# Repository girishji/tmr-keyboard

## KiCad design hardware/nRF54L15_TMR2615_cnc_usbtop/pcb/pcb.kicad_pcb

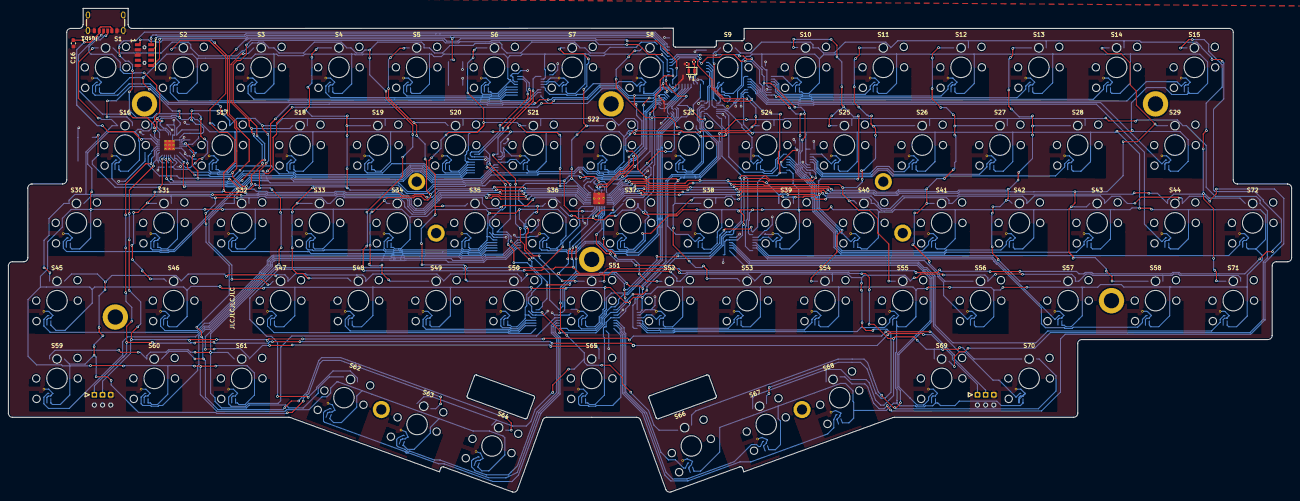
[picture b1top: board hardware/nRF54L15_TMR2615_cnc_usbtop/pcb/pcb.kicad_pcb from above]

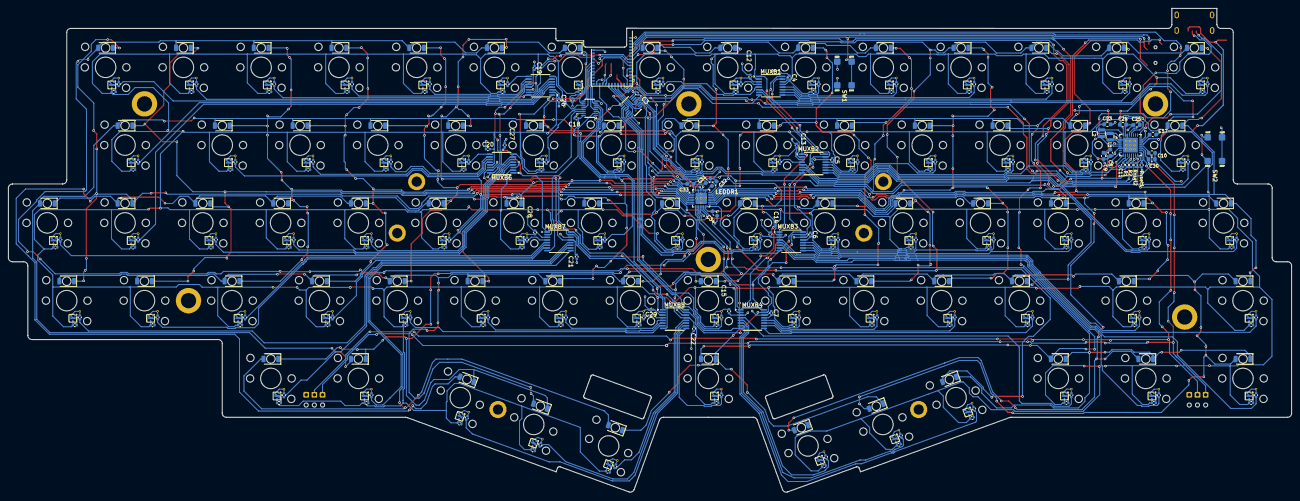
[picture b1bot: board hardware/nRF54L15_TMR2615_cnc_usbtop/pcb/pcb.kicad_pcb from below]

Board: 2 copper layers, 313.5 x 118.2 mm, 435 parts (340 on the bottom side), 142 nets.

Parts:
BAT1, BAT2: PCB_Wire_Solder_3p_Connector
C1, C2: 12pF; C_0402_1005Metric
C3, C4, C5, C6, C7, C12, C13, C14, C15, C18, C19, C20, C21, C22, C26, C27, C28, C29: .1uF; C_0402_1005Metric
C8, C9, C10, C23, C24: 10uF; C_0603_1608Metric
C11: 0.1uF; C_0402_1005Metric
C16, C17, C32, C33, C34: 1uF; C_0603_1608Metric
C25, C30: 2.2uF; C_0603_1608Metric
C31: 1nF; C_0603_1608Metric
Cvcc1, Cvcc2, Cvcc3, Cvcc4, Cvcc5, Cvcc6, Cvcc7, Cvcc8, Cvcc9, Cvcc10, Cvcc11, Cvcc12, Cvcc13, Cvcc14, Cvcc15, Cvcc16, Cvcc17, Cvcc18, Cvcc19, Cvcc20, Cvcc21, Cvcc22, Cvcc23, Cvcc24, Cvcc25, Cvcc26, Cvcc27, Cvcc28, Cvcc29, Cvcc30, Cvcc31, Cvcc32, Cvcc33, Cvcc34, Cvcc35, Cvcc36, Cvcc37, Cvcc38, Cvcc39, Cvcc40, Cvcc41, Cvcc42, Cvcc43, Cvcc44, Cvcc45, Cvcc46, Cvcc47, Cvcc48, Cvcc49, Cvcc50, Cvcc51, Cvcc52, Cvcc53, Cvcc54, Cvcc55, Cvcc56, Cvcc57, Cvcc58, Cvcc59, Cvcc60, Cvcc61, Cvcc62, Cvcc63, Cvcc64, Cvcc65, Cvcc66, Cvcc67, Cvcc68, Cvcc69, Cvcc70, Cvcc71, Cvcc72: 0.1uF; C_0402_1005Metric_Cvcc
Cvout1, Cvout2, Cvout3, Cvout4, Cvout5, Cvout6, Cvout7, Cvout8, Cvout9, Cvout10, Cvout11, Cvout12, Cvout13, Cvout14, Cvout15, Cvout16, Cvout17, Cvout18, Cvout19, Cvout20, Cvout21, Cvout22, Cvout23, Cvout24, Cvout25, Cvout26, Cvout27, Cvout28, Cvout29, Cvout30, Cvout31, Cvout32, Cvout33, Cvout34, Cvout35, Cvout36, Cvout37, Cvout38, Cvout39, Cvout40, Cvout41, Cvout42, Cvout43, Cvout44, Cvout45, Cvout46, Cvout47, Cvout48, Cvout49, Cvout50, Cvout51, Cvout52, Cvout53, Cvout54, Cvout55, Cvout56, Cvout57, Cvout58, Cvout59, Cvout60, Cvout61, Cvout62, Cvout63, Cvout64, Cvout65, Cvout66, Cvout67, Cvout68, Cvout69, Cvout70, Cvout71, Cvout72: 0.1nF; C_0402_1005Metric_Cvout
D1, D2, D3, D4, D5, D6, D7, D8, D9, D10, D11, D12, D13, D14, D15, D16, D17, D18, D19, D20, D21, D22, D23, D24, D25, D26, D27, D28, D29, D30, D31, D32, D33, D34, D35, D36, D37, D38, D39, D40, D41, D42, D43, D44, D45, D46, D47, D48, D49, D50, D51, D52, D53, D54, D55, D56, D57, D58, D59, D60, D61, D62, D63, D64, D65, D66, D67, D68, D69, D70, D71, D72: Green LED; LED_1206_3216Metric_ReverseMount_Hole2.1mm
Hm1, Hm2: M1.4_smtso; SMTSO_M1.4_M1.6
Hs1, Hs2, Hs3, Hs4, Hs5, Hs10: M2_Pad; SMTSO_M2
Hs6, Hs7, Hs8, Hs9: M2_Pad; SMTSO_M1.4_M1.6
JLC1: JLC_Order_Num
JTAG1: Conn_ARM_JTAG_SWD_10; SAMTEC-CLP-105-02-X-D-A
Jusb1: USB_C_Receptacle_PowerOnly_6P; USB_C_Receptacle_GCT_USB4125-xx-x_6P_TopMnt_Horizontal
L1, L2: 2.2uH; L_Samsung_CIGT201610EH2R2MNE
LEDDR1: LP5864; LP5864-VQFN-32-1EP_4x4mm_P0.4mm_EP2.8x2.8mm_ThermalVias
M1: Ezurio BL54L15 (nrf54L15) module; Ezurio_BL54L15_Module
MUXA1, MUXA2: TMUX1574DYY; Texas_DYY0016A_TSOT-23-16_2x4.2mm_P0.5mm
MUXB1, MUXB2, MUXB3, MUXB4, MUXB5, MUXB6, MUXB7, MUXB8: TMUX1108PW; TSSOP-16_4.4x5mm_P0.65mm
PMIC1: nPM1300-QEXX; QFN-32-1EP_5x5mm_P0.5mm_EP3.6x3.6mm_ThermalVias
R1, R2: 10k; R_0402_1005Metric
Rvset1: 47k; R_0402_1005Metric
Rvset2: 4.7k; R_0402_1005Metric
S1, S2, S3, S4, S5, S6, S7, S8, S9, S10, S11, S12, S13, S14, S15, S16, S17, S18, S19, S20, S21, S22, S23, S24, S25, S26, S27, S28, S29, S30, S31, S32, S33, S34, S35, S36, S37, S38, S39, S40, S41, S42, S43, S44, S45, S46, S47, S48, S49, S50, S51, S52, S53, S54, S55, S56, S57, S58, S59, S60, S61, S62, S63, S64, S65, S66, S67, S68, S69, S70, S71, S72: Switch; Kailh_gateron_sw_lowpro
SW1, SW2: SW_DIP_x01; Aliexpress_SW_TACT_4x4x1.5mm
Stb1, Stb2: TMR_switch_stab_2.0u; Stabilizer_Lowpro_2U
TMR1, TMR2, TMR3, TMR4, TMR5, TMR6, TMR7, TMR8, TMR9, TMR10, TMR11, TMR12, TMR13, TMR14, TMR15, TMR16, TMR17, TMR18, TMR19, TMR20, TMR21, TMR22, TMR23, TMR24, TMR25, TMR26, TMR27, TMR28, TMR29, TMR30, TMR31, TMR32, TMR33, TMR34, TMR35, TMR36, TMR37, TMR38, TMR39, TMR40, TMR41, TMR42, TMR43, TMR44, TMR45, TMR46, TMR47, TMR48, TMR49, TMR50, TMR51, TMR52, TMR53, TMR54, TMR55, TMR56, TMR57, TMR58, TMR59, TMR60, TMR61, TMR62, TMR63, TMR64, TMR65, TMR66, TMR67, TMR68, TMR69, TMR70, TMR71, TMR72: TMR2615; TMR2615-DFN-3L-1.6x1.6
Y1: 32.768 kHz; Crystal_SMD_2012-2Pin_2.0x1.2mm

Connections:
/AIN0: M1.23 (P1.04/AIN0/CLK), MUXA1.4 (D1)
/AIN1: M1.22 (P1.05/AIN1), MUXA1.7 (D2)
/AIN2: M1.21 (P1.06/AIN2), MUXA1.9 (D3)
/AIN3: M1.20 (P1.07/AIN3), MUXA1.12 (D4)
/AIN4: M1.35 (P1.11/AIN4/CLK), MUXA2.9 (D3)
/AIN5: M1.34 (P1.12/AIN5/CLK), MUXA2.12 (D4)
/AIN6: M1.33 (P1.13/AIN6), MUXA2.4 (D1)
/AIN7: M1.32 (P1.14/AIN7), MUXA2.7 (D2)
/ANA_01: Cvout1.1, MUXB1.7 (S4), TMR1.1 (V_{OUT})
/ANA_02: Cvout2.1, MUXB1.6 (S3), TMR2.1 (V_{OUT})
/ANA_03: Cvout3.1, MUXB1.9 (S8), TMR3.1 (V_{OUT})
/ANA_04: Cvout4.1, MUXB1.10 (S7), TMR4.1 (V_{OUT})
/ANA_05: Cvout5.1, MUXB1.11 (S6), TMR5.1 (V_{OUT})
/ANA_06: Cvout6.1, MUXB1.12 (S5), TMR6.1 (V_{OUT})
/ANA_07: Cvout7.1, MUXB1.4 (S1), TMR7.1 (V_{OUT})
/ANA_08: Cvout8.1, MUXB1.5 (S2), TMR8.1 (V_{OUT})
/ANA_09: Cvout9.1, MUXA2.10 (S3B), TMR9.1 (V_{OUT})
/ANA_10: Cvout10.1, MUXB5.9 (S8), TMR10.1 (V_{OUT})
/ANA_11: Cvout11.1, MUXB5.10 (S7), TMR11.1 (V_{OUT})
/ANA_12: Cvout12.1, MUXB5.11 (S6), TMR12.1 (V_{OUT})
/ANA_13: Cvout13.1, MUXB5.12 (S5), TMR13.1 (V_{OUT})
/ANA_14: Cvout14.1, MUXB5.7 (S4), TMR14.1 (V_{OUT})
/ANA_15: Cvout15.1, MUXB5.6 (S3), TMR15.1 (V_{OUT})
/ANA_16: Cvout16.1, MUXB2.5 (S2), TMR16.1 (V_{OUT})
/ANA_17: Cvout17.1, MUXB2.9 (S8), TMR17.1 (V_{OUT})
/ANA_18: Cvout18.1, MUXB2.10 (S7), TMR18.1 (V_{OUT})
/ANA_19: Cvout19.1, MUXB2.11 (S6), TMR19.1 (V_{OUT})
/ANA_20: Cvout20.1, MUXB2.12 (S5), TMR20.1 (V_{OUT})
/ANA_21: Cvout21.1, MUXB2.4 (S1), TMR21.1 (V_{OUT})
/ANA_22: Cvout22.1, MUXA1.13 (S4B), TMR22.1 (V_{OUT})
/ANA_23: Cvout23.1, MUXA2.6 (S2B), TMR23.1 (V_{OUT})
/ANA_24: Cvout24.1, MUXA2.13 (S4B), TMR24.1 (V_{OUT})
/ANA_25: Cvout25.1, MUXB6.9 (S8), TMR25.1 (V_{OUT})
/ANA_26: Cvout26.1, MUXB6.10 (S7), TMR26.1 (V_{OUT})
/ANA_27: Cvout27.1, MUXB6.11 (S6), TMR27.1 (V_{OUT})
/ANA_28: Cvout28.1, MUXB6.12 (S5), TMR28.1 (V_{OUT})
/ANA_29: Cvout29.1, MUXB5.5 (S2), TMR29.1 (V_{OUT})
/ANA_30: Cvout30.1, MUXB2.7 (S4), TMR30.1 (V_{OUT})
/ANA_31: Cvout31.1, MUXB2.6 (S3), TMR31.1 (V_{OUT})
/ANA_32: Cvout32.1, MUXB3.9 (S8), TMR32.1 (V_{OUT})
/ANA_33: Cvout33.1, MUXB3.10 (S7), TMR33.1 (V_{OUT})
/ANA_34: Cvout34.1, MUXB3.11 (S6), TMR34.1 (V_{OUT})
/ANA_35: Cvout35.1, MUXB3.12 (S5), TMR35.1 (V_{OUT})
/ANA_36: Cvout36.1, MUXA1.6 (S2B), TMR36.1 (V_{OUT})
/ANA_37: Cvout37.1, MUXA1.10 (S3B), TMR37.1 (V_{OUT})
/ANA_38: Cvout38.1, MUXA2.3 (S1B), TMR38.1 (V_{OUT})
/ANA_39: Cvout39.1, MUXB7.4 (S1), TMR39.1 (V_{OUT})
/ANA_40: Cvout40.1, MUXB6.7 (S4), TMR40.1 (V_{OUT})
/ANA_41: Cvout41.1, MUXB6.6 (S3), TMR41.1 (V_{OUT})
/ANA_42: Cvout42.1, MUXB6.5 (S2), TMR42.1 (V_{OUT})
/ANA_43: Cvout43.1, MUXB6.4 (S1), TMR43.1 (V_{OUT})
/ANA_44: Cvout44.1, MUXB5.4 (S1), TMR44.1 (V_{OUT})
/ANA_45: Cvout45.1, MUXB3.5 (S2), TMR45.1 (V_{OUT})
/ANA_46: Cvout46.1, MUXB3.4 (S1), TMR46.1 (V_{OUT})
/ANA_47: Cvout47.1, MUXB4.9 (S8), TMR47.1 (V_{OUT})
/ANA_48: Cvout48.1, MUXB4.10 (S7), TMR48.1 (V_{OUT})
/ANA_49: Cvout49.1, MUXB4.11 (S6), TMR49.1 (V_{OUT})
/ANA_50: Cvout50.1, MUXB4.12 (S5), TMR50.1 (V_{OUT})
/ANA_51: Cvout51.1, MUXA1.3 (S1B), TMR51.1 (V_{OUT})
/ANA_52: Cvout52.1, MUXB8.4 (S1), TMR52.1 (V_{OUT})
/ANA_53: Cvout53.1, MUXB8.5 (S2), TMR53.1 (V_{OUT})
/ANA_54: Cvout54.1, MUXB8.6 (S3), TMR54.1 (V_{OUT})
/ANA_55: Cvout55.1, MUXB8.7 (S4), TMR55.1 (V_{OUT})
/ANA_56: Cvout56.1, MUXB7.12 (S5), TMR56.1 (V_{OUT})
/ANA_57: Cvout57.1, MUXB7.6 (S3), TMR57.1 (V_{OUT})
/ANA_58: Cvout58.1, MUXB7.7 (S4), TMR58.1 (V_{OUT})
/ANA_59: Cvout59.1, MUXB3.6 (S3), TMR59.1 (V_{OUT})
/ANA_60: Cvout60.1, MUXB3.7 (S4), TMR60.1 (V_{OUT})
/ANA_61: Cvout61.1, MUXB4.4 (S1), TMR61.1 (V_{OUT})
/ANA_62: Cvout62.1, MUXB4.7 (S4), TMR62.1 (V_{OUT})
/ANA_63: Cvout63.1, MUXB4.6 (S3), TMR63.1 (V_{OUT})
/ANA_64: Cvout64.1, MUXB4.5 (S2), TMR64.1 (V_{OUT})
/ANA_65: Cvout65.1, MUXB8.9 (S8), TMR65.1 (V_{OUT})
/ANA_66: Cvout66.1, MUXB8.12 (S5), TMR66.1 (V_{OUT})
/ANA_67: Cvout67.1, MUXB8.11 (S6), TMR67.1 (V_{OUT})
/ANA_68: Cvout68.1, MUXB8.10 (S7), TMR68.1 (V_{OUT})
/ANA_69: Cvout69.1, MUXB7.9 (S8), TMR69.1 (V_{OUT})
/ANA_70: Cvout70.1, MUXB7.10 (S7), TMR70.1 (V_{OUT})
/ANA_71: Cvout71.1, MUXB7.11 (S6), TMR71.1 (V_{OUT})
/ANA_72: Cvout72.1, MUXB7.5 (S2), TMR72.1 (V_{OUT})
/CS0: D9.1 (K), D24.1 (K), D38.1 (K), D53.1 (K), LEDDR1.2 (CS0)
/CS1: D10.1 (K), D25.1 (K), D39.1 (K), D54.1 (K), LEDDR1.3 (CS1)
/CS2: D11.1 (K), D26.1 (K), D40.1 (K), D55.1 (K), LEDDR1.4 (CS2)
/CS3: D12.1 (K), D27.1 (K), D41.1 (K), D56.1 (K), LEDDR1.5 (CS3)
/CS4: D13.1 (K), D28.1 (K), D42.1 (K), D57.1 (K), LEDDR1.6 (CS4)
/CS5: D14.1 (K), D29.1 (K), D43.1 (K), D58.1 (K), LEDDR1.7 (CS5)
/CS6: D15.1 (K), D44.1 (K), D71.1 (K), D72.1 (K), LEDDR1.8 (CS6)
/CS7: D67.1 (K), D68.1 (K), D69.1 (K), D70.1 (K), LEDDR1.9 (CS7)
/CS8: D63.1 (K), D64.1 (K), D65.1 (K), D66.1 (K), LEDDR1.10 (CS8)
/CS9: D59.1 (K), D60.1 (K), D61.1 (K), D62.1 (K), LEDDR1.16 (CS9)
/CS10: D1.1 (K), D16.1 (K), D30.1 (K), D45.1 (K), LEDDR1.17 (CS10)
/CS11: D2.1 (K), D17.1 (K), D31.1 (K), D46.1 (K), LEDDR1.18 (CS11)
/CS12: D3.1 (K), D18.1 (K), D32.1 (K), D47.1 (K), LEDDR1.19 (CS12)
/CS13: D4.1 (K), D19.1 (K), D33.1 (K), D48.1 (K), LEDDR1.20 (CS13)
/CS14: D5.1 (K), D20.1 (K), D34.1 (K), D49.1 (K), LEDDR1.21 (CS14)
/CS15: D6.1 (K), D21.1 (K), D35.1 (K), D50.1 (K), LEDDR1.22 (CS15)
/CS16: D7.1 (K), D22.1 (K), D36.1 (K), D51.1 (K), LEDDR1.23 (CS16)
/CS17: D8.1 (K), D23.1 (K), D37.1 (K), D52.1 (K), LEDDR1.24 (CS17)
/GPIO_X: M1.4 (P2.07), PMIC1.10 (GPIO3)
/INT: M1.17 (P0.00), PMIC1.8 (GPIO1)
/LED_DR_EN: C31.1, LEDDR1.32 (VIO_EN), M1.11 (P2.04)
/LOADSW_CTRL: M1.12 (P2.05), PMIC1.9 (GPIO2)
/MUXA_SEL: M1.13 (P2.03), MUXA1.1 (SEL), MUXA2.1 (SEL)
/MUXB_SEL_0: M1.9 (P2.00), MUXB1.1 (A0), MUXB2.1 (A0), MUXB3.1 (A0), MUXB4.1 (A0), MUXB5.1 (A0), MUXB6.1 (A0), MUXB7.1 (A0), MUXB8.1 (A0)
/MUXB_SEL_1: M1.10 (P2.01/CLK), MUXB1.16 (A1), MUXB2.16 (A1), MUXB3.16 (A1), MUXB4.16 (A1), MUXB5.16 (A1), MUXB6.16 (A1), MUXB7.16 (A1), MUXB8.16 (A1)
/MUXB_SEL_2: M1.8 (P2.02), MUXB1.15 (A2), MUXB2.15 (A2), MUXB3.15 (A2), MUXB4.15 (A2), MUXB5.15 (A2), MUXB6.15 (A2), MUXB7.15 (A2), MUXB8.15 (A2)
/MUX_B_1: MUXA1.14 (S4A), MUXB1.8 (D)
/MUX_B_2: MUXA1.11 (S3A), MUXB2.8 (D)
/MUX_B_3: MUXA1.5 (S2A), MUXB3.8 (D)
/MUX_B_4: MUXA1.2 (S1A), MUXB4.8 (D)
/MUX_B_5: MUXA2.11 (S3A), MUXB5.8 (D)
/MUX_B_6: MUXA2.14 (S4A), MUXB6.8 (D)
/MUX_B_7: MUXA2.2 (S1A), MUXB7.8 (D)
/MUX_B_8: MUXA2.5 (S2A), MUXB8.8 (D)
/NRESET: JTAG1.10 (~RESET), M1.7 (NRESET), SW1.2
/SCL: LEDDR1.28 (SCL_SCLK), M1.18 (P0.01), PMIC1.14 (SCL), R1.2
/SDA: LEDDR1.29 (SDA_MOSI), M1.19 (P0.02), PMIC1.13 (SDA), R2.2
/SW0: D1.2 (A), D2.2 (A), D3.2 (A), D4.2 (A), D5.2 (A), D6.2 (A), D7.2 (A), D8.2 (A), D9.2 (A), D10.2 (A), D11.2 (A), D12.2 (A), D13.2 (A), D14.2 (A), D15.2 (A), D62.2 (A), D66.2 (A), D70.2 (A), LEDDR1.11 (SW0)
/SW1: D16.2 (A), D17.2 (A), D18.2 (A), D19.2 (A), D20.2 (A), D21.2 (A), D22.2 (A), D23.2 (A), D24.2 (A), D25.2 (A), D26.2 (A), D27.2 (A), D28.2 (A), D29.2 (A), D61.2 (A), D65.2 (A), D69.2 (A), D72.2 (A), LEDDR1.12 (SW1)
/SW2: D30.2 (A), D31.2 (A), D32.2 (A), D33.2 (A), D34.2 (A), D35.2 (A), D36.2 (A), D37.2 (A), D38.2 (A), D39.2 (A), D40.2 (A), D41.2 (A), D42.2 (A), D43.2 (A), D44.2 (A), D60.2 (A), D64.2 (A), D68.2 (A), LEDDR1.13 (SW2)
/SW3: D45.2 (A), D46.2 (A), D47.2 (A), D48.2 (A), D49.2 (A), D50.2 (A), D51.2 (A), D52.2 (A), D53.2 (A), D54.2 (A), D55.2 (A), D56.2 (A), D57.2 (A), D58.2 (A), D59.2 (A), D63.2 (A), D67.2 (A), D71.2 (A), LEDDR1.14 (SW3)
/SWDCLK: JTAG1.4 (SWCLK/TCK), M1.6 (SWDCLK)
/SWDIO: JTAG1.2 (SWDIO/TMS), M1.5 (SWDIO)
/VBAT: BAT1.1 (VBAT), BAT2.1 (VBAT), C30.1, PMIC1.19 (VBAT)
/VBUSOUT: C17.1, PMIC1.22 (VBUSOUT)
/VDD_nRF: C11.2, C23.1, JTAG1.1 (VTref), L1.1, M1.26 (VDD_nRF), PMIC1.1 (VOUT1), PMIC1.12 (VDDIO), R1.1, R2.1
/VOUT2: C24.1, L2.1, PMIC1.28 (LSIN1/VINLDO1), PMIC1.32 (VOUT2)
/VSYS: C8.1, C9.1, C10.1, C33.1, C34.1, LEDDR1.1 (VCC), LEDDR1.15 (VLED), PMIC1.4 (PVDD), PMIC1.20 (VSYS)
GND: BAT1.3 (GND), BAT2.3 (GND), C1.2, C2.2, C3.1, C4.1, C5.1, C6.1, C7.1, C8.2, C9.2, C10.2, C11.1, C12.1, C12.2, C13.1, C13.2, C14.1, C14.2, C15.1, C15.2, C16.2, C17.2, C18.1, C19.1, C20.1, C21.1, C22.1, C23.2, C24.2, C25.2, C26.1, C26.2, C27.1, C27.2, C28.1, C28.2, C29.1, C29.2, C30.2, C31.2, C32.1, C33.2, C34.2, Cvcc1.2, Cvcc2.2, Cvcc3.2, Cvcc4.2, Cvcc5.2, Cvcc6.2, Cvcc7.2, Cvcc8.2, Cvcc9.2, Cvcc10.2, Cvcc11.2, Cvcc12.2, Cvcc13.2, Cvcc14.2, Cvcc15.2, Cvcc16.2, Cvcc17.2, Cvcc18.2, Cvcc19.2, Cvcc20.2, Cvcc21.2, Cvcc22.2, Cvcc23.2, Cvcc24.2, Cvcc25.2, Cvcc26.2, Cvcc27.2, Cvcc28.2, Cvcc29.2, Cvcc30.2, Cvcc31.2, Cvcc32.2, Cvcc33.2, Cvcc34.2, Cvcc35.2, Cvcc36.2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
unnamed: BAT1.2 (NTC), BAT2.2 (NTC), PMIC1.18 (NTC)
unnamed: Jusb1.A5 (CC1), PMIC1.23 (CC1)
unnamed: Jusb1.B5 (CC2), PMIC1.24 (CC2)
unnamed: C32.2, LEDDR1.25 (VCAP)
unnamed: C1.1, M1.25 (P1.00/XL1), Y1.1
unnamed: C2.1, M1.24 (P1.01/XL2), Y1.2
unnamed: PMIC1.15 (SHPHLD), SW2.2
unnamed: L1.2, PMIC1.3 (SW1)
unnamed: L2.2, PMIC1.5 (SW2)
unnamed: C16.1, Jusb1.A9 (VBUS), Jusb1.B9 (VBUS), PMIC1.21 (VBUS)
unnamed: PMIC1.17 (VSET1), Rvset1.2
unnamed: PMIC1.16 (VSET2), Rvset2.2
VCCS: C3.2, C4.2, C5.2, C6.2, C7.2, C18.2, C19.2, C20.2, C21.2, C22.2, C25.1, Cvcc1.1, Cvcc2.1, Cvcc3.1, Cvcc4.1, Cvcc5.1, Cvcc6.1, Cvcc7.1, Cvcc8.1, Cvcc9.1, Cvcc10.1, Cvcc11.1, Cvcc12.1, Cvcc13.1, Cvcc14.1, Cvcc15.1, Cvcc16.1, Cvcc17.1, Cvcc18.1, Cvcc19.1, Cvcc20.1, Cvcc21.1, Cvcc22.1, Cvcc23.1, Cvcc24.1, Cvcc25.1, Cvcc26.1, Cvcc27.1, Cvcc28.1, Cvcc29.1, Cvcc30.1, Cvcc31.1, Cvcc32.1, Cvcc33.1, Cvcc34.1, Cvcc35.1, Cvcc36.1, Cvcc37.1, Cvcc38.1, Cvcc39.1, Cvcc40.1, Cvcc41.1, Cvcc42.1, Cvcc43.1, Cvcc44.1, Cvcc45.1, Cvcc46.1, Cvcc47.1, Cvcc48.1, Cvcc49.1, Cvcc50.1, Cvcc51.1, Cvcc52.1, Cvcc53.1, Cvcc54.1, Cvcc55.1, Cvcc56.1, Cvcc57.1, Cvcc58.1, Cvcc59.1, Cvcc60.1, Cvcc61.1, Cvcc62.1, Cvcc63.1, Cvcc64.1, Cvcc65.1, Cvcc66.1, Cvcc67.1, Cvcc68.1, Cvcc69.1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

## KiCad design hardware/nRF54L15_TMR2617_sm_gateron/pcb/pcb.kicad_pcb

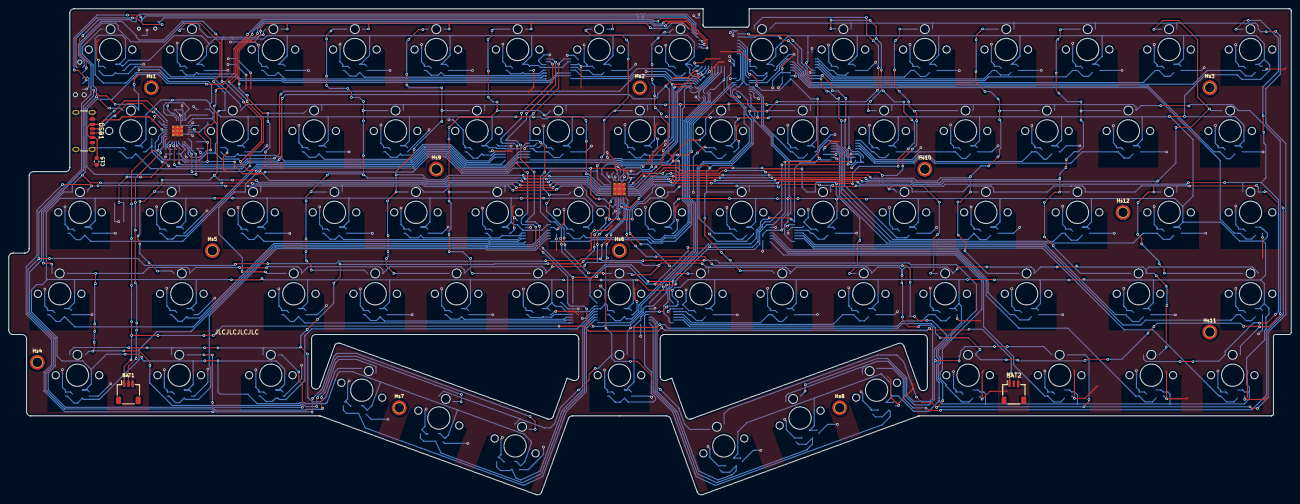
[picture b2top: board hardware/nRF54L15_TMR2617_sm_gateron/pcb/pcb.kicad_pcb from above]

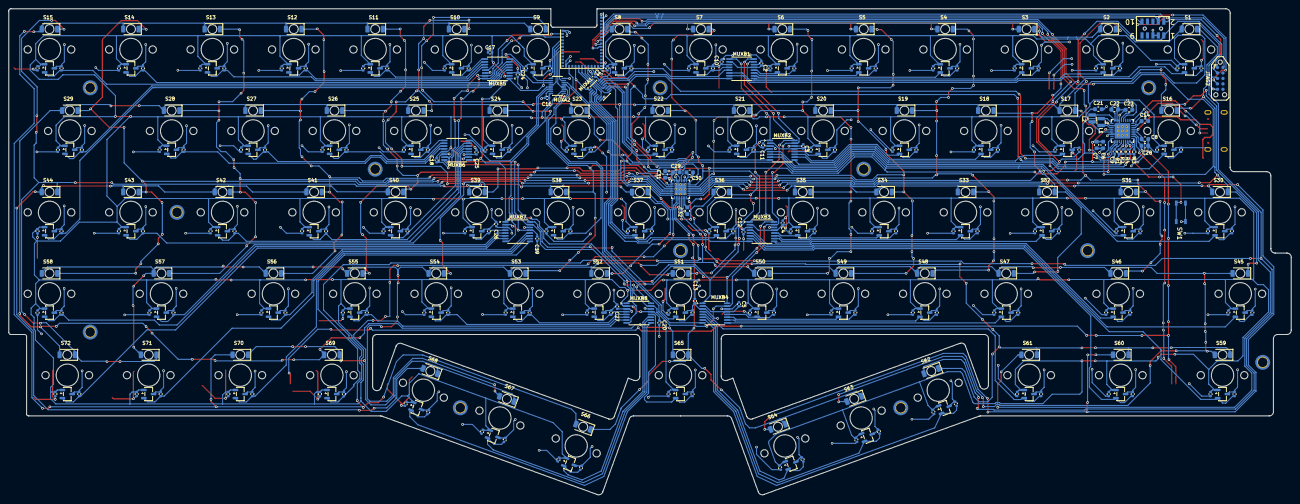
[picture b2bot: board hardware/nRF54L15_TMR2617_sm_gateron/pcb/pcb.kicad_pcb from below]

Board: 2 copper layers, 299.2 x 113.4 mm, 432 parts (341 on the bottom side), 140 nets.

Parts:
BAT1, BAT2: JST_SH_SM03B-SRSS-TB_1x03-1MP_P1.00mm_Horizontal
C1, C2, C3, C4, C5, C10, C11, C12, C13, C16, C17, C18, C19, C20, C24, C25, C26, C27: .1uF; C_0402_1005Metric
C6, C7, C8, C21, C22: 10uF; C_0603_1608Metric
C9: 0.1uF; C_0402_1005Metric
C14, C15, C30, C31, C32: 1uF; C_0603_1608Metric
C23, C28: 2.2uF; C_0603_1608Metric
C29: 1nF; C_0603_1608Metric
Cvcc1, Cvcc2, Cvcc3, Cvcc4, Cvcc5, Cvcc6, Cvcc7, Cvcc8, Cvcc9, Cvcc10, Cvcc11, Cvcc12, Cvcc13, Cvcc14, Cvcc15, Cvcc16, Cvcc17, Cvcc18, Cvcc19, Cvcc20, Cvcc21, Cvcc22, Cvcc23, Cvcc24, Cvcc25, Cvcc26, Cvcc27, Cvcc28, Cvcc29, Cvcc30, Cvcc31, Cvcc32, Cvcc33, Cvcc34, Cvcc35, Cvcc36, Cvcc37, Cvcc38, Cvcc39, Cvcc40, Cvcc41, Cvcc42, Cvcc43, Cvcc44, Cvcc45, Cvcc46, Cvcc47, Cvcc48, Cvcc49, Cvcc50, Cvcc51, Cvcc52, Cvcc53, Cvcc54, Cvcc55, Cvcc56, Cvcc57, Cvcc58, Cvcc59, Cvcc60, Cvcc61, Cvcc62, Cvcc63, Cvcc64, Cvcc65, Cvcc66, Cvcc67, Cvcc68, Cvcc69, Cvcc70, Cvcc71, Cvcc72: 0.1uF; C_0402_1005Metric
Cvout1, Cvout2, Cvout3, Cvout4, Cvout5, Cvout6, Cvout7, Cvout8, Cvout9, Cvout10, Cvout11, Cvout12, Cvout13, Cvout14, Cvout15, Cvout16, Cvout17, Cvout18, Cvout19, Cvout20, Cvout21, Cvout22, Cvout23, Cvout24, Cvout25, Cvout26, Cvout27, Cvout28, Cvout29, Cvout30, Cvout31, Cvout32, Cvout33, Cvout34, Cvout35, Cvout36, Cvout37, Cvout38, Cvout39, Cvout40, Cvout41, Cvout42, Cvout43, Cvout44, Cvout45, Cvout46, Cvout47, Cvout48, Cvout49, Cvout50, Cvout51, Cvout52, Cvout53, Cvout54, Cvout55, Cvout56, Cvout57, Cvout58, Cvout59, Cvout60, Cvout61, Cvout62, Cvout63, Cvout64, Cvout65, Cvout66, Cvout67, Cvout68, Cvout69, Cvout70, Cvout71, Cvout72: 0.1nF; C_0402_1005Metric
D1, D2, D3, D4, D5, D6, D7, D8, D9, D10, D11, D12, D13, D14, D15, D16, D17, D18, D19, D20, D21, D22, D23, D24, D25, D26, D27, D28, D29, D30, D31, D32, D33, D34, D35, D36, D37, D38, D39, D40, D41, D42, D43, D44, D45, D46, D47, D48, D49, D50, D51, D52, D53, D54, D55, D56, D57, D58, D59, D60, D61, D62, D63, D64, D65, D66, D67, D68, D69, D70, D71, D72: Green LED; LED_1206_3216Metric_ReverseMount_Hole2.1mm
Hs1, Hs2, Hs3, Hs4, Hs5, Hs6, Hs7, Hs8, Hs9, Hs10, Hs11, Hs12: M2_Pad; MountingHole_2.2mm_M2_ISO7380_Pad_TopBottom
JLC1: JLC_Order_Num
JTAG1: Conn_02x05_Odd_Even; SAMTEC-CLP-105-02-X-D-A
JTAG2: Conn_02x05_Odd_Even; Tag-Connect_TC2050-IDC-NL_2x05_P1.27mm_Vertical
L1, L2: 2.2uH; L_Samsung_CIGT201610EH2R2MNE
LEDDR1: LP5864; VQFN-32-1EP_4x4mm_P0.4mm_EP2.8x2.8mm_ThermalVias
M1: Ezurio BL54L15 (nrf54L15) module; Ezurio_BL54L15_Module
MUXA1, MUXA2: TMUX1574DYY; Texas_DYY0016A_TSOT-23-16_2x4.2mm_P0.5mm
MUXB1, MUXB2, MUXB3, MUXB4, MUXB5, MUXB6, MUXB7, MUXB8: TMUX1108PW; TSSOP-16_4.4x5mm_P0.65mm
PMIC1: nPM1300-QEXX; QFN-32-1EP_5x5mm_P0.5mm_EP3.6x3.6mm_ThermalVias
R1, R2: 10k; R_0402_1005Metric
R3, R4: 47k; R_0402_1005Metric
S1, S2, S3, S4, S5, S6, S7, S8, S9, S10, S11, S12, S13, S14, S15, S16, S17, S18, S19, S20, S21, S22, S23, S24, S25, S26, S27, S28, S29, S30, S31, S32, S33, S34, S35, S36, S37, S38, S39, S40, S41, S42, S43, S44, S45, S46, S47, S48, S49, S50, S51, S52, S53, S54, S55, S56, S57, S58, S59, S60, S61, S62, S63, S64, S65, S66, S67, S68, S69, S70, S71, S72: Switch; Gateron_Switch_Lowpro
SW1: SW_DIP_x01; Button_Switch_3x4x2.5
Stb1, Stb2: TMR_switch_stab_2.0u; Stabilizer_Lowpro_2U
TMR1, TMR2, TMR3, TMR4, TMR5, TMR6, TMR7, TMR8, TMR9, TMR10, TMR11, TMR12, TMR13, TMR14, TMR15, TMR16, TMR17, TMR18, TMR19, TMR20, TMR21, TMR22, TMR23, TMR24, TMR25, TMR26, TMR27, TMR28, TMR29, TMR30, TMR31, TMR32, TMR33, TMR34, TMR35, TMR36, TMR37, TMR38, TMR39, TMR40, TMR41, TMR42, TMR43, TMR44, TMR45, TMR46, TMR47, TMR48, TMR49, TMR50, TMR51, TMR52, TMR53, TMR54, TMR55, TMR56, TMR57, TMR58, TMR59, TMR60, TMR61, TMR62, TMR63, TMR64, TMR65, TMR66, TMR67, TMR68, TMR69, TMR70, TMR71, TMR72: TMR2617; SOT-23-3
USB1: USB_C_Receptacle_PowerOnly_6P; USB_C_Receptacle_GCT_USB4125-xx-x-0190_6P_TopMnt_Horizontal

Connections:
/AIN0: M1.23 (P1.04/AIN0/CLK), MUXA1.4 (D1)
/AIN1: M1.22 (P1.05/AIN1), MUXA1.7 (D2)
/AIN2: M1.21 (P1.06/AIN2), MUXA1.9 (D3)
/AIN3: M1.20 (P1.07/AIN3), MUXA1.12 (D4)
/AIN4: M1.35 (P1.11/AIN4/CLK), MUXA2.9 (D3)
/AIN5: M1.34 (P1.12/AIN5/CLK), MUXA2.12 (D4)
/AIN6: M1.33 (P1.13/AIN6), MUXA2.4 (D1)
/AIN7: M1.32 (P1.14/AIN7), MUXA2.7 (D2)
/ANA_01: Cvout1.1, MUXB1.7 (S4), TMR1.2 (V_{OUT})
/ANA_02: Cvout2.1, MUXB1.6 (S3), TMR2.2 (V_{OUT})
/ANA_03: Cvout3.1, MUXB1.9 (S8), TMR3.2 (V_{OUT})
/ANA_04: Cvout4.1, MUXB1.10 (S7), TMR4.2 (V_{OUT})
/ANA_05: Cvout5.1, MUXB1.11 (S6), TMR5.2 (V_{OUT})
/ANA_06: Cvout6.1, MUXB1.12 (S5), TMR6.2 (V_{OUT})
/ANA_07: Cvout7.1, MUXB1.4 (S1), TMR7.2 (V_{OUT})
/ANA_08: Cvout8.1, MUXB1.5 (S2), TMR8.2 (V_{OUT})
/ANA_09: Cvout9.1, MUXA2.10 (S3B), TMR9.2 (V_{OUT})
/ANA_10: Cvout10.1, MUXB5.9 (S8), TMR10.2 (V_{OUT})
/ANA_11: Cvout11.1, MUXB5.10 (S7), TMR11.2 (V_{OUT})
/ANA_12: Cvout12.1, MUXB5.11 (S6), TMR12.2 (V_{OUT})
/ANA_13: Cvout13.1, MUXB5.12 (S5), TMR13.2 (V_{OUT})
/ANA_14: Cvout14.1, MUXB5.7 (S4), TMR14.2 (V_{OUT})
/ANA_15: Cvout15.1, MUXB5.6 (S3), TMR15.2 (V_{OUT})
/ANA_16: Cvout16.1, MUXB2.5 (S2), TMR16.2 (V_{OUT})
/ANA_17: Cvout17.1, MUXB2.9 (S8), TMR17.2 (V_{OUT})
/ANA_18: Cvout18.1, MUXB2.10 (S7), TMR18.2 (V_{OUT})
/ANA_19: Cvout19.1, MUXB2.11 (S6), TMR19.2 (V_{OUT})
/ANA_20: Cvout20.1, MUXB2.12 (S5), TMR20.2 (V_{OUT})
/ANA_21: Cvout21.1, MUXB2.4 (S1), TMR21.2 (V_{OUT})
/ANA_22: Cvout22.1, MUXA1.13 (S4B), TMR22.2 (V_{OUT})
/ANA_23: Cvout23.1, MUXA2.6 (S2B), TMR23.2 (V_{OUT})
/ANA_24: Cvout24.1, MUXA2.13 (S4B), TMR24.2 (V_{OUT})
/ANA_25: Cvout25.1, MUXB6.9 (S8), TMR25.2 (V_{OUT})
/ANA_26: Cvout26.1, MUXB6.10 (S7), TMR26.2 (V_{OUT})
/ANA_27: Cvout27.1, MUXB6.11 (S6), TMR27.2 (V_{OUT})
/ANA_28: Cvout28.1, MUXB6.12 (S5), TMR28.2 (V_{OUT})
/ANA_29: Cvout29.1, MUXB5.5 (S2), TMR29.2 (V_{OUT})
/ANA_30: Cvout30.1, MUXB2.7 (S4), TMR30.2 (V_{OUT})
/ANA_31: Cvout31.1, MUXB2.6 (S3), TMR31.2 (V_{OUT})
/ANA_32: Cvout32.1, MUXB3.9 (S8), TMR32.2 (V_{OUT})
/ANA_33: Cvout33.1, MUXB3.10 (S7), TMR33.2 (V_{OUT})
/ANA_34: Cvout34.1, MUXB3.11 (S6), TMR34.2 (V_{OUT})
/ANA_35: Cvout35.1, MUXB3.12 (S5), TMR35.2 (V_{OUT})
/ANA_36: Cvout36.1, MUXA1.6 (S2B), TMR36.2 (V_{OUT})
/ANA_37: Cvout37.1, MUXA1.10 (S3B), TMR37.2 (V_{OUT})
/ANA_38: Cvout38.1, MUXA2.3 (S1B), TMR38.2 (V_{OUT})
/ANA_39: Cvout39.1, MUXB7.4 (S1), TMR39.2 (V_{OUT})
/ANA_40: Cvout40.1, MUXB6.7 (S4), TMR40.2 (V_{OUT})
/ANA_41: Cvout41.1, MUXB6.6 (S3), TMR41.2 (V_{OUT})
/ANA_42: Cvout42.1, MUXB6.5 (S2), TMR42.2 (V_{OUT})
/ANA_43: Cvout43.1, MUXB6.4 (S1), TMR43.2 (V_{OUT})
/ANA_44: Cvout44.1, MUXB5.4 (S1), TMR44.2 (V_{OUT})
/ANA_45: Cvout45.1, MUXB3.5 (S2), TMR45.2 (V_{OUT})
/ANA_46: Cvout46.1, MUXB3.4 (S1), TMR46.2 (V_{OUT})
/ANA_47: Cvout47.1, MUXB4.9 (S8), TMR47.2 (V_{OUT})
/ANA_48: Cvout48.1, MUXB4.10 (S7), TMR48.2 (V_{OUT})
/ANA_49: Cvout49.1, MUXB4.11 (S6), TMR49.2 (V_{OUT})
/ANA_50: Cvout50.1, MUXB4.12 (S5), TMR50.2 (V_{OUT})
/ANA_51: Cvout51.1, MUXA1.3 (S1B), TMR51.2 (V_{OUT})
/ANA_52: Cvout52.1, MUXB8.4 (S1), TMR52.2 (V_{OUT})
/ANA_53: Cvout53.1, MUXB8.5 (S2), TMR53.2 (V_{OUT})
/ANA_54: Cvout54.1, MUXB8.6 (S3), TMR54.2 (V_{OUT})
/ANA_55: Cvout55.1, MUXB8.7 (S4), TMR55.2 (V_{OUT})
/ANA_56: Cvout56.1, MUXB7.12 (S5), TMR56.2 (V_{OUT})
/ANA_57: Cvout57.1, MUXB7.5 (S2), TMR57.2 (V_{OUT})
/ANA_58: Cvout58.1, MUXB7.6 (S3), TMR58.2 (V_{OUT})
/ANA_59: Cvout59.1, MUXB3.6 (S3), TMR59.2 (V_{OUT})
/ANA_60: Cvout60.1, MUXB3.7 (S4), TMR60.2 (V_{OUT})
/ANA_61: Cvout61.1, MUXB4.4 (S1), TMR61.2 (V_{OUT})
/ANA_62: Cvout62.1, MUXB4.7 (S4), TMR62.2 (V_{OUT})
/ANA_63: Cvout63.1, MUXB4.6 (S3), TMR63.2 (V_{OUT})
/ANA_64: Cvout64.1, MUXB4.5 (S2), TMR64.2 (V_{OUT})
/ANA_65: Cvout65.1, MUXB8.12 (S5), TMR65.2 (V_{OUT})
/ANA_66: Cvout66.1, MUXB8.11 (S6), TMR66.2 (V_{OUT})
/ANA_67: Cvout67.1, MUXB8.10 (S7), TMR67.2 (V_{OUT})
/ANA_68: Cvout68.1, MUXB8.9 (S8), TMR68.2 (V_{OUT})
/ANA_69: Cvout69.1, MUXB7.9 (S8), TMR69.2 (V_{OUT})
/ANA_70: Cvout70.1, MUXB7.10 (S7), TMR70.2 (V_{OUT})
/ANA_71: Cvout71.1, MUXB7.11 (S6), TMR71.2 (V_{OUT})
/ANA_72: Cvout72.1, MUXB7.7 (S4), TMR72.2 (V_{OUT})
/CS0: D9.1 (K), D24.1 (K), D38.1 (K), D53.1 (K), LEDDR1.2 (CS0)
/CS1: D10.1 (K), D25.1 (K), D39.1 (K), D54.1 (K), LEDDR1.3 (CS1)
/CS2: D11.1 (K), D26.1 (K), D40.1 (K), D55.1 (K), LEDDR1.4 (CS2)
/CS3: D12.1 (K), D27.1 (K), D41.1 (K), D56.1 (K), LEDDR1.5 (CS3)
/CS4: D13.1 (K), D28.1 (K), D42.1 (K), D57.1 (K), LEDDR1.6 (CS4)
/CS5: D14.1 (K), D29.1 (K), D43.1 (K), D58.1 (K), LEDDR1.7 (CS5)
/CS6: D15.1 (K), D44.1 (K), D71.1 (K), D72.1 (K), LEDDR1.8 (CS6)
/CS7: D67.1 (K), D68.1 (K), D69.1 (K), D70.1 (K), LEDDR1.9 (CS7)
/CS8: D63.1 (K), D64.1 (K), D65.1 (K), D66.1 (K), LEDDR1.10 (CS8)
/CS9: D59.1 (K), D60.1 (K), D61.1 (K), D62.1 (K), LEDDR1.16 (CS9)
/CS10: D1.1 (K), D16.1 (K), D30.1 (K), D45.1 (K), LEDDR1.17 (CS10)
/CS11: D2.1 (K), D17.1 (K), D31.1 (K), D46.1 (K), LEDDR1.18 (CS11)
/CS12: D3.1 (K), D18.1 (K), D32.1 (K), D47.1 (K), LEDDR1.19 (CS12)
/CS13: D4.1 (K), D19.1 (K), D33.1 (K), D48.1 (K), LEDDR1.20 (CS13)
/CS14: D5.1 (K), D20.1 (K), D34.1 (K), D49.1 (K), LEDDR1.21 (CS14)
/CS15: D6.1 (K), D21.1 (K), D35.1 (K), D50.1 (K), LEDDR1.22 (CS15)
/CS16: D7.1 (K), D22.1 (K), D36.1 (K), D51.1 (K), LEDDR1.23 (CS16)
/CS17: D8.1 (K), D23.1 (K), D37.1 (K), D52.1 (K), LEDDR1.24 (CS17)
/GPIO_X: M1.8 (P2.02), PMIC1.10 (GPIO3)
/INT: M1.10 (P2.01/CLK), PMIC1.8 (GPIO1)
/LED_DR_EN: C29.1, LEDDR1.32 (VIO_EN), M1.19 (P0.02)
/LOADSW_CTRL: M1.9 (P2.00), PMIC1.9 (GPIO2)
/MUXA_SEL: M1.24 (P1.01/XL2), MUXA1.1 (SEL), MUXA2.1 (SEL)
/MUXB_SEL_0: M1.36 (P0.03/CLK), MUXB1.1 (A0), MUXB2.1 (A0), MUXB3.1 (A0), MUXB4.1 (A0), MUXB5.1 (A0), MUXB6.1 (A0), MUXB7.1 (A0), MUXB8.1 (A0)
/MUXB_SEL_1: M1.37 (P2.10), MUXB1.16 (A1), MUXB2.16 (A1), MUXB3.16 (A1), MUXB4.16 (A1), MUXB5.16 (A1), MUXB6.16 (A1), MUXB7.16 (A1), MUXB8.16 (A1)
/MUXB_SEL_2: M1.38 (P2.06/CLK), MUXB1.15 (A2), MUXB2.15 (A2), MUXB3.15 (A2), MUXB4.15 (A2), MUXB5.15 (A2), MUXB6.15 (A2), MUXB7.15 (A2), MUXB8.15 (A2)
/MUX_B_1: MUXA1.14 (S4A), MUXB1.8 (D)
/MUX_B_2: MUXA1.11 (S3A), MUXB2.8 (D)
/MUX_B_3: MUXA1.5 (S2A), MUXB3.8 (D)
/MUX_B_4: MUXA1.2 (S1A), MUXB4.8 (D)
/MUX_B_5: MUXA2.11 (S3A), MUXB5.8 (D)
/MUX_B_6: MUXA2.14 (S4A), MUXB6.8 (D)
/MUX_B_7: MUXA2.2 (S1A), MUXB7.8 (D)
/MUX_B_8: MUXA2.5 (S2A), MUXB8.8 (D)
/NRESET: JTAG1.10, JTAG2.10, M1.7 (NRESET)
/SCL: LEDDR1.28 (SCL_SCLK), M1.17 (P0.00), PMIC1.14 (SCL), R1.2
/SDA: LEDDR1.29 (SDA_MOSI), M1.18 (P0.01), PMIC1.13 (SDA), R2.2
/SW0: D1.2 (A), D2.2 (A), D3.2 (A), D4.2 (A), D5.2 (A), D6.2 (A), D7.2 (A), D8.2 (A), D9.2 (A), D10.2 (A), D11.2 (A), D12.2 (A), D13.2 (A), D14.2 (A), D15.2 (A), D62.2 (A), D66.2 (A), D70.2 (A), LEDDR1.11 (SW0)
/SW1: D16.2 (A), D17.2 (A), D18.2 (A), D19.2 (A), D20.2 (A), D21.2 (A), D22.2 (A), D23.2 (A), D24.2 (A), D25.2 (A), D26.2 (A), D27.2 (A), D28.2 (A), D29.2 (A), D61.2 (A), D65.2 (A), D69.2 (A), D72.2 (A), LEDDR1.12 (SW1)
/SW2: D30.2 (A), D31.2 (A), D32.2 (A), D33.2 (A), D34.2 (A), D35.2 (A), D36.2 (A), D37.2 (A), D38.2 (A), D39.2 (A), D40.2 (A), D41.2 (A), D42.2 (A), D43.2 (A), D44.2 (A), D60.2 (A), D64.2 (A), D68.2 (A), LEDDR1.13 (SW2)
/SW3: D45.2 (A), D46.2 (A), D47.2 (A), D48.2 (A), D49.2 (A), D50.2 (A), D51.2 (A), D52.2 (A), D53.2 (A), D54.2 (A), D55.2 (A), D56.2 (A), D57.2 (A), D58.2 (A), D59.2 (A), D63.2 (A), D67.2 (A), D71.2 (A), LEDDR1.14 (SW3)
/SWDCLK: JTAG1.4, JTAG2.4, M1.6 (SWDCLK)
/SWDIO: JTAG1.2, JTAG2.2, M1.5 (SWDIO)
/VBAT: BAT1.1 (VBAT), BAT2.1 (VBAT), C28.1, PMIC1.19 (VBAT)
/VDDIO: C9.2, C21.1, JTAG1.1, JTAG2.1, L1.1, M1.26 (VDD_nRF), PMIC1.1 (VOUT1), PMIC1.12 (VDDIO), R1.1, R2.1
/VOUT2: C22.1, L2.1, PMIC1.28 (LSIN1/VINLDO1), PMIC1.32 (VOUT2)
/VSYS: C6.1, C7.1, C8.1, C31.1, C32.1, LEDDR1.1 (VCC), LEDDR1.15 (VLED), PMIC1.4 (PVDD), PMIC1.20 (VSYS)
GND: BAT1.3 (GND), BAT2.3 (GND), C1.1, C2.1, C3.1, C4.1, C5.1, C6.2, C7.2, C8.2, C9.1, C10.1, C10.2, C11.1, C11.2, C12.1, C12.2, C13.1, C13.2, C14.2, C15.2, C16.1, C17.1, C18.1, C19.1, C20.1, C21.2, C22.2, C23.2, C24.1, C24.2, C25.1, C25.2, C26.1, C26.2, C27.1, C27.2, C28.2, C29.2, C30.1, C31.2, C32.2, Cvcc1.2, Cvcc2.2, Cvcc3.2, Cvcc4.2, Cvcc5.2, Cvcc6.2, Cvcc7.2, Cvcc8.2, Cvcc9.2, Cvcc10.2, Cvcc11.2, Cvcc12.2, Cvcc13.2, Cvcc14.2, Cvcc15.2, Cvcc16.2, Cvcc17.2, Cvcc18.2, Cvcc19.2, Cvcc20.2, Cvcc21.2, Cvcc22.2, Cvcc23.2, Cvcc24.2, Cvcc25.2, Cvcc26.2, Cvcc27.2, Cvcc28.2, Cvcc29.2, Cvcc30.2, Cvcc31.2, Cvcc32.2, Cvcc33.2, Cvcc34.2, Cvcc35.2, Cvcc36.2, Cvcc37.2, Cvcc38.2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
unnamed: BAT1.2 (NTC), PMIC1.18 (NTC)
unnamed: C30.2, LEDDR1.25 (VCAP)
unnamed: PMIC1.23 (CC1), USB1.A5 (CC1)
unnamed: PMIC1.24 (CC2), USB1.B5 (CC2)
unnamed: PMIC1.15 (SHPHLD), SW1.2
unnamed: L1.2, PMIC1.3 (SW1)
unnamed: L2.2, PMIC1.5 (SW2)
unnamed: C15.1, PMIC1.21 (VBUS), USB1.A9 (VBUS), USB1.B9 (VBUS)
unnamed: C14.1, PMIC1.22 (VBUSOUT)
unnamed: PMIC1.17 (VSET1), R3.2
unnamed: PMIC1.16 (VSET2), R4.2
VCCS: C1.2, C2.2, C3.2, C4.2, C5.2, C16.2, C17.2, C18.2, C19.2, C20.2, C23.1, Cvcc1.1, Cvcc2.1, Cvcc3.1, Cvcc4.1, Cvcc5.1, Cvcc6.1, Cvcc7.1, Cvcc8.1, Cvcc9.1, Cvcc10.1, Cvcc11.1, Cvcc12.1, Cvcc13.1, Cvcc14.1, Cvcc15.1, Cvcc16.1, Cvcc17.1, Cvcc18.1, Cvcc19.1, Cvcc20.1, Cvcc21.1, Cvcc22.1, Cvcc23.1, Cvcc24.1, Cvcc25.1, Cvcc26.1, Cvcc27.1, Cvcc28.1, Cvcc29.1, Cvcc30.1, Cvcc31.1, Cvcc32.1, Cvcc33.1, Cvcc34.1, Cvcc35.1, Cvcc36.1, Cvcc37.1, Cvcc38.1, Cvcc39.1, Cvcc40.1, Cvcc41.1, Cvcc42.1, Cvcc43.1, Cvcc44.1, Cvcc45.1, Cvcc46.1, Cvcc47.1, Cvcc48.1, Cvcc49.1, Cvcc50.1, Cvcc51.1, Cvcc52.1, Cvcc53.1, Cvcc54.1, Cvcc55.1, Cvcc56.1, Cvcc57.1, Cvcc58.1, Cvcc59.1, Cvcc60.1, Cvcc61.1, Cvcc62.1, Cvcc63.1, Cvcc64.1, Cvcc65.1, Cvcc66.1, Cvcc67.1, Cvcc68.1, Cvcc69.1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
